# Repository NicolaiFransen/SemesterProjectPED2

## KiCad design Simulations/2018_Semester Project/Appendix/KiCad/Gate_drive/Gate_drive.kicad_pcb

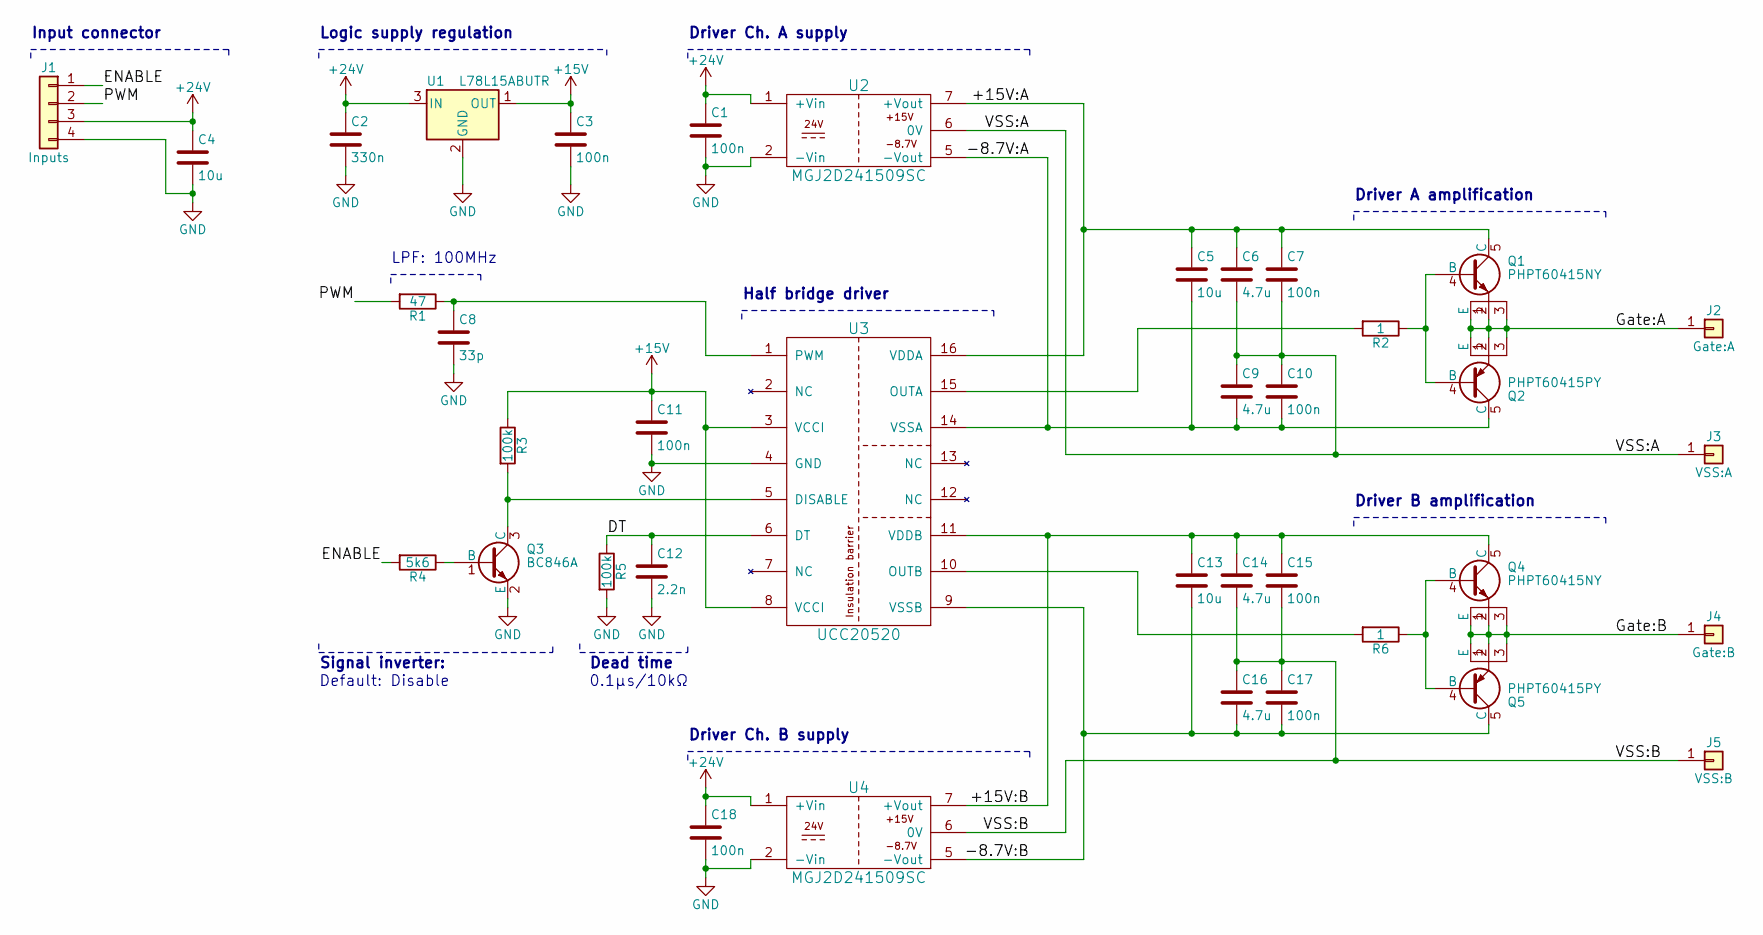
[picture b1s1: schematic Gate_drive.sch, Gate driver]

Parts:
C1, C3, C7, C10, C11, C15, C17, C18: 100n; C_1206
C2: 330n; C_1206
C4, C5, C13: 10u; C_1206
C6, C9, C14, C16: 4.7u; C_1206
C8: 33p; C_1206
C12: 2.2n; C_1206
J1: Inputs; Molex_KK-6410-04_04x2.54mm_Straight
J2: Gate:A; SolderWirePad_2x_1-2mmDrill
J3: VSS:A; SolderWirePad_single_1-2mmDrill
J4: Gate:B; SolderWirePad_2x_1-2mmDrill
J5: VSS:B; SolderWirePad_single_1-2mmDrill
Q1, Q4: PHPT60415NY; SOT-669_LFPAK
Q2, Q5: PHPT60415PY; SOT-669_LFPAK
Q3: BC846A; SOT-23
R1: 47; R_1206
R2, R6: 1; R_1206
R3, R5: 100k; R_1206
R4: 5k6; R_1206
U1: L78L15ABUTR; SOT-89-3
U2, U4: MGJ2D241509SC; SIL_MGJ2
U3: UCC20520; SOIC-16W_7.5x10.3mm_Pitch1.27mm

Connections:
+15V: C3.1, C11.1, R3.1, U1.1 (OUT), U3.3 (VCCI), U3.8 (VCCI)
+24V: C1.1, C2.1, C4.1, C18.1, J1.3, U1.3 (IN), U2.1 (+Vin), U4.1 (+Vin)
/+15V:A: C5.1, C6.1, C7.1, Q1.5 (C), U2.7 (+Vout), U3.16 (VDDA)
/+15V:B: C13.1, C14.1, C15.1, Q4.5 (C), U3.11 (VDDB), U4.7 (+Vout)
/-8.7V:A: C5.2, C9.2, C10.2, Q2.5 (C), U2.5 (-Vout), U3.14 (VSSA)
/-8.7V:B: C13.2, C16.2, C17.2, Q5.5 (C), U3.9 (VSSB), U4.5 (-Vout)
/DT: C12.1, R5.1, U3.6 (DT)
/ENABLE: J1.1, R4.2
/Gate:A: J2.1, Q1.1 (E), Q1.2, Q1.3, Q2.1 (E), Q2.2, Q2.3
/Gate:B: J4.1, Q4.1 (E), Q4.2, Q4.3, Q5.1 (E), Q5.2, Q5.3
/PWM: J1.2, R1.2
/VSS:A: C6.2, C7.2, C9.1, C10.1, J3.1, U2.6 (0V)
/VSS:B: C14.2, C15.2, C16.1, C17.1, J5.1, U4.6 (0V)
GND: C1.2, C2.2, C3.2, C4.2, C8.2, C11.2, C12.2, C18.2, J1.4, Q3.2 (E), R5.2, U1.2 (GND), U2.2 (-Vin), U3.4 (GND), U4.2 (-Vin)
unnamed: C8.1, R1.1, U3.1 (PWM)
unnamed: Q1.4 (B), Q2.4 (B), R2.1
unnamed: Q3.1 (B), R4.1
unnamed: Q3.3 (C), R3.2, U3.5 (DISABLE)
unnamed: Q4.4 (B), Q5.4 (B), R6.1
unnamed: R2.2, U3.15 (OUTA)
unnamed: R6.2, U3.10 (OUTB)

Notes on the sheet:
Dead time
LPF: 100MHz
Input connector
Logic supply regulation
Driver Ch. A supply
Driver Ch. B supply
Driver A amplification
Driver B amplification
Half bridge driver
Signal inverter:
0.1µs/10kΩ
Default: Disable

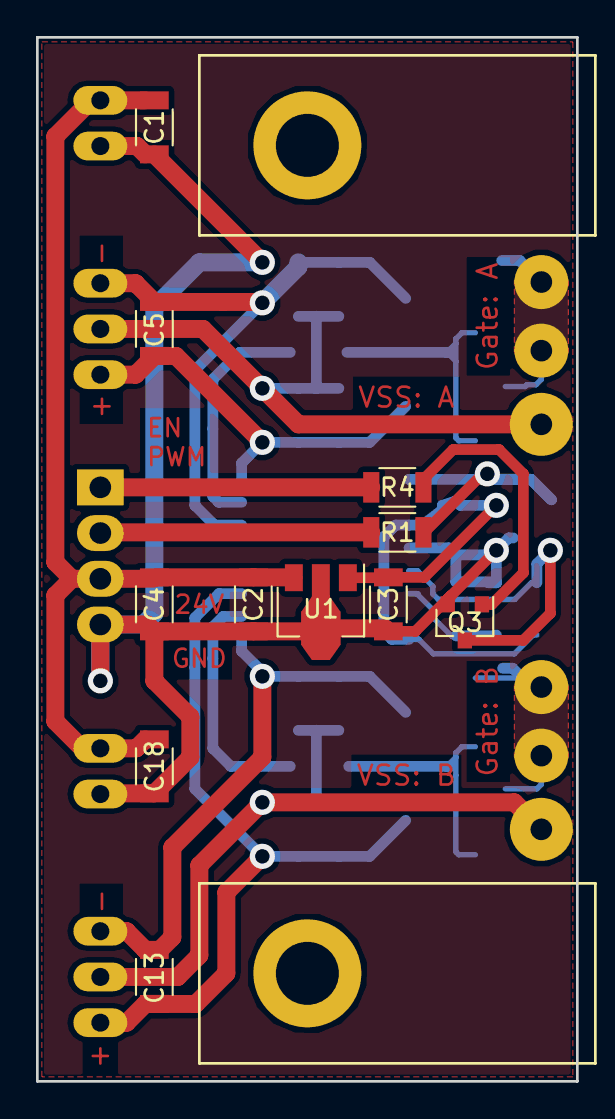
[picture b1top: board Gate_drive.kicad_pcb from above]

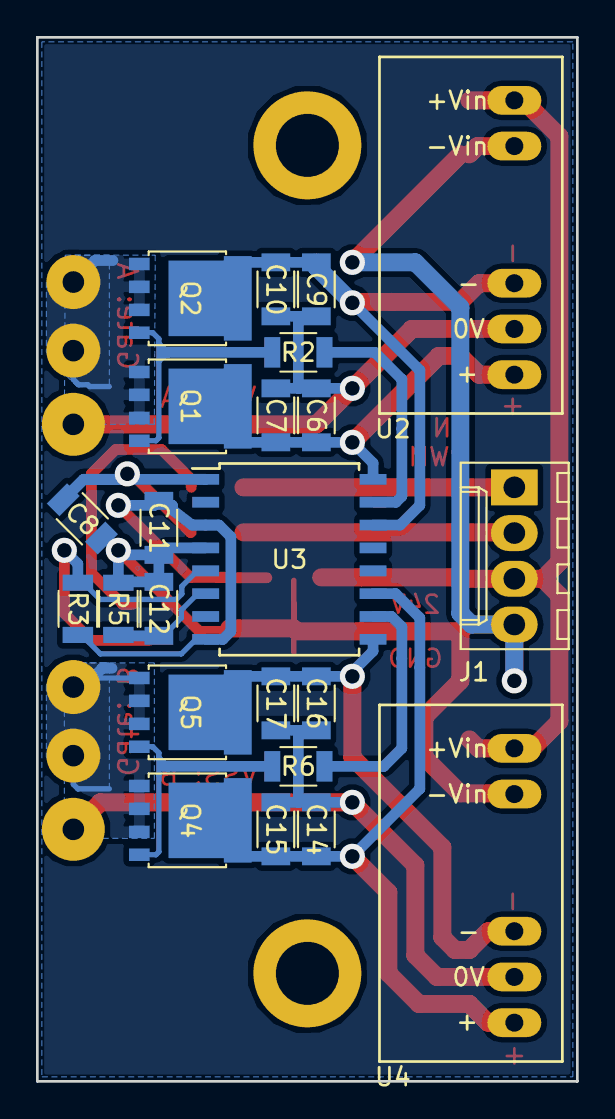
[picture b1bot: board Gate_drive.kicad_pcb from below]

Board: 2 copper layers, 30.0 x 58.0 mm, 38 parts (23 on the bottom side), 21 nets.

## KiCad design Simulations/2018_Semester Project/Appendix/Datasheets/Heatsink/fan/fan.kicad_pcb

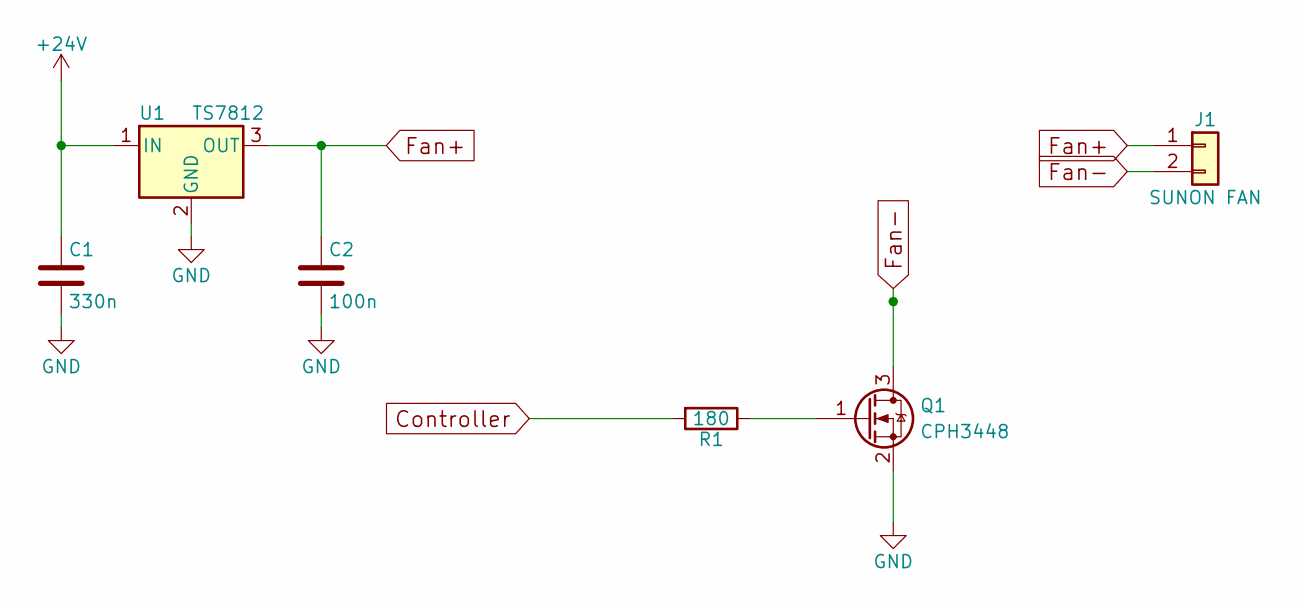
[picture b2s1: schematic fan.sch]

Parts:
C1: 330n; C_1206
C2: 100n; C_1206
J1: SUNON FAN; Molex_KK-6410-02_02x2.54mm_Straight
Q1: CPH3448; SOT-23
R1: 180; R_1206
U1: TS7812; TO-220-3_Horizontal

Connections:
+24V: C1.1, U1.1 (IN)
Controller: R1.2
Fan+: C2.1, J1.1, U1.3 (OUT)
Fan-: J1.2, Q1.3 (D)
GND: C1.2, C2.2, Q1.2 (S), U1.2 (GND)
unnamed: Q1.1 (G), R1.1

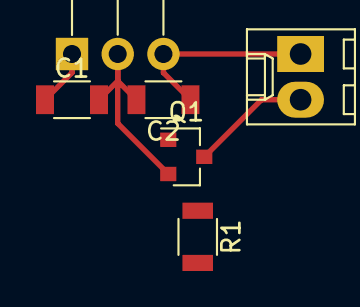
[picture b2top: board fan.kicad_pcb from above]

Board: 2 copper layers, 6 parts (0 on the bottom side), 5 nets.

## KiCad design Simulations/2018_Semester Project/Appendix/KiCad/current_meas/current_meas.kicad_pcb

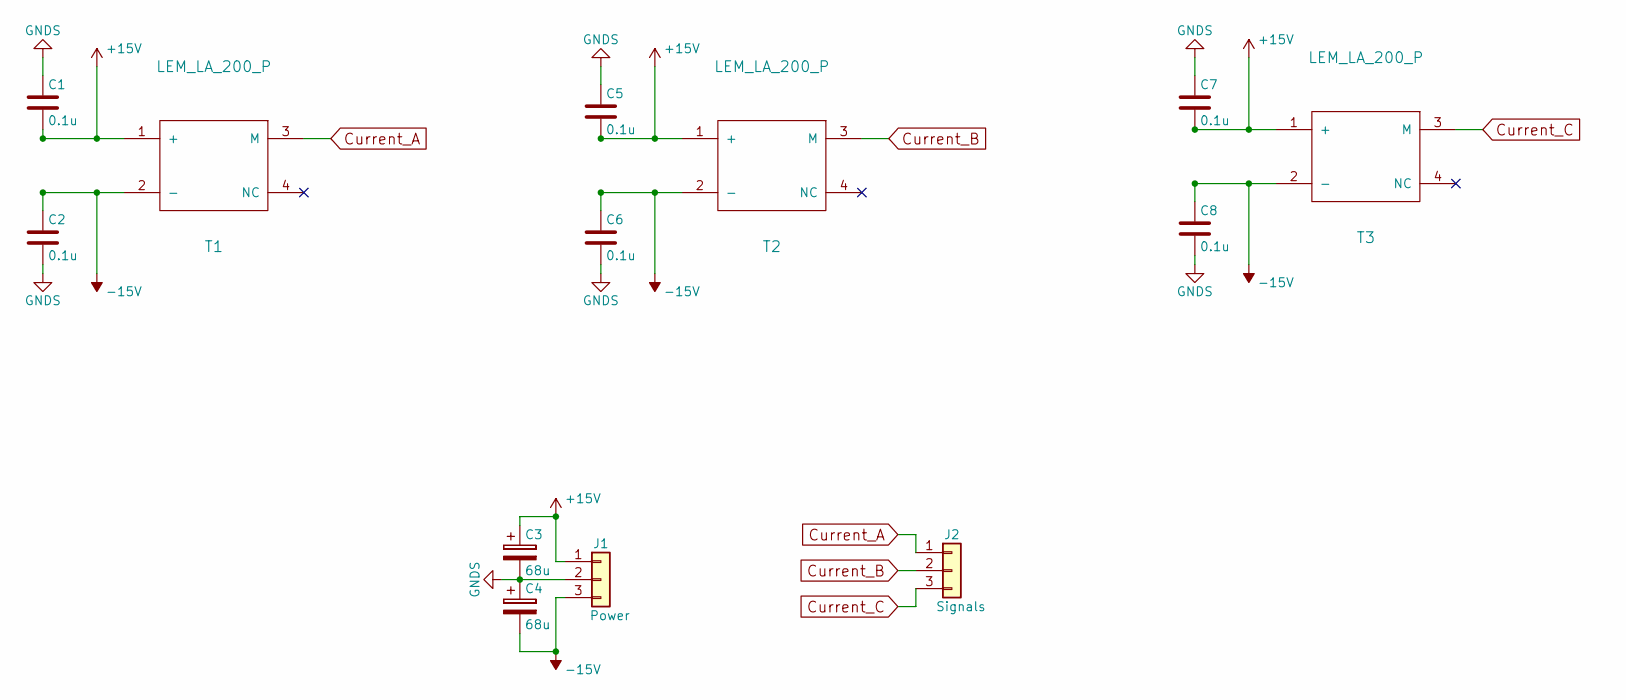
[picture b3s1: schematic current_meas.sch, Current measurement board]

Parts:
C1, C2, C5, C6, C7, C8: 0.1u; C_1206_HandSoldering
C3, C4: 68u; CP_Radial_D6.3mm_P2.50mm
J1: Power; Molex_KK-6410-03_03x2.54mm_Straight
J2: Signals; Molex_KK-6410-03_03x2.54mm_Straight
T1, T2, T3: LEM_LA_200_P; LEM_200

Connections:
+15V: C1.2, C3.1, C5.2, C7.2, J1.1, T1.1 (+), T2.1 (+), T3.1 (+)
-15V: C2.1, C4.2, C6.1, C8.1, J1.3, T1.2 (-), T2.2 (-), T3.2 (-)
Current_A: J2.1, T1.3 (M)
Current_B: J2.2, T2.3 (M)
Current_C: J2.3, T3.3 (M)
GNDS: C1.1, C2.2, C3.2, C4.1, C5.1, C6.2, C7.1, C8.2, J1.2

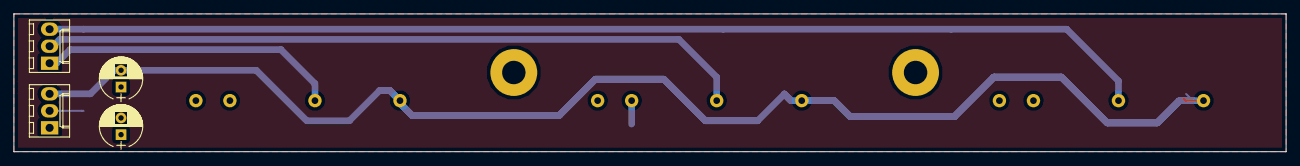
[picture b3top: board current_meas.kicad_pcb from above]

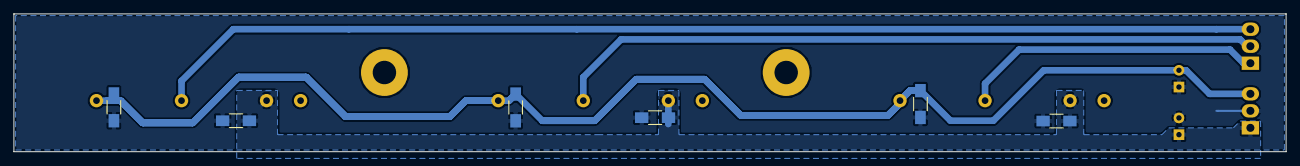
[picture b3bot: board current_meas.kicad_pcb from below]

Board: 2 copper layers, 190.0 x 20.6 mm, 13 parts (6 on the bottom side), 6 nets.

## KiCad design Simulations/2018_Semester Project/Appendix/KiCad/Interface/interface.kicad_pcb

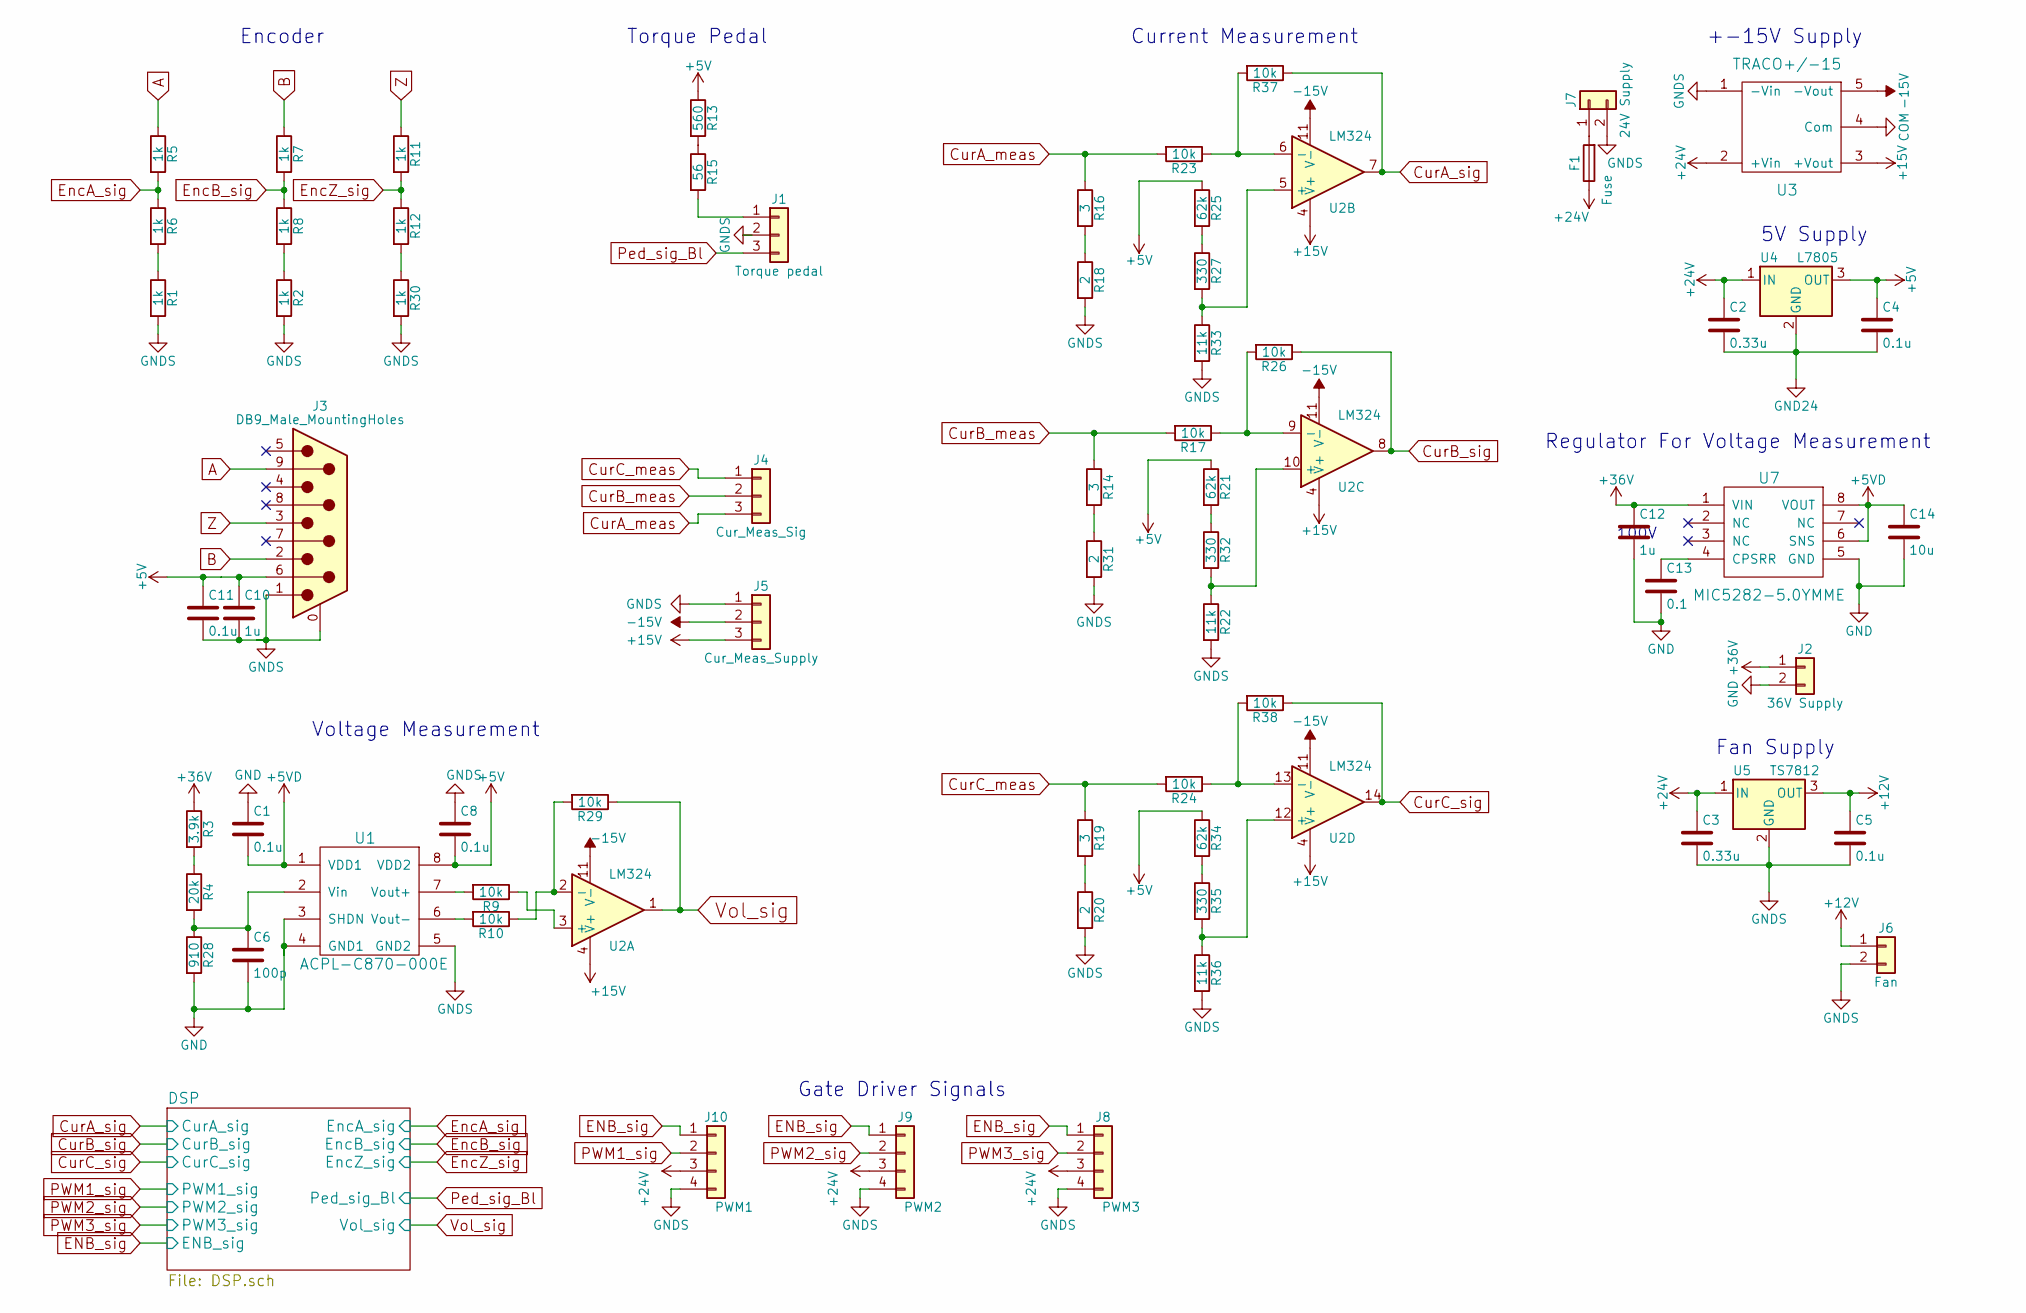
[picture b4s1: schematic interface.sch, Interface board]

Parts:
C1, C4, C5, C8, C11: 0.1u; C_1206
C2, C3: 0.33u; C_1206
C6: 100p; C_1206
C10, C12: 1u; C_1206
C13: 0.1; C_1206
C14: 10u; C_1206
F1: Fuse; Fuseholder5x20_horiz_open_Schurter_0031_8201
J1: Torque pedal; Molex_KK-6410-03_03x2.54mm_Straight
J2: 36V Supply; Molex_KK-6410-02_02x2.54mm_Straight
J3: DB9_Male_MountingHoles; DMR-09-P
J4: Cur_Meas_Sig; Molex_KK-6410-03_03x2.54mm_Straight
J5: Cur_Meas_Supply; Molex_KK-6410-03_03x2.54mm_Straight
J6: Fan; Molex_KK-6410-02_02x2.54mm_Straight
J7: 24V Supply; Molex_KK-6410-02_02x2.54mm_Straight
J8: PWM3; Molex_KK-6410-04_04x2.54mm_Straight
J9: PWM2; Molex_KK-6410-04_04x2.54mm_Straight
J10: PWM1; Molex_KK-6410-04_04x2.54mm_Straight
R1, R2, R5, R6, R7, R8, R11, R12, R30: 1k; R_1206
R3: 3.9k; R_1206
R4: 20k; R_1206
R9, R10, R17, R23, R24, R26, R29, R37, R38: 10k; R_1206
R13: 560; R_1206
R14, R16, R19: 3; R_1206
R15: 56; R_1206
R18, R20, R31: 2; R_1206
R21, R25, R34: 62k; R_1206
R22, R33, R36: 11k; R_1206
R27, R32, R35: 330; R_1206
R28: 910; R_1206
U1: ACPL-C870-000E
U2: LM324; SOIC-14_3.9x8.7mm_Pitch1.27mm
U3: TRACO+/-15; DCDC-Conv_TRACO_TEN10-XXXX_Dual
U4: L7805; TO-220-3_Horizontal
U5: TS7812; TO-220-3_Horizontal
U7: MIC5282-5.0YMME; 8-Pin(ePad)MSOP

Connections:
+5V: C4.1, C8.2, C10.1, C11.1, J3.6, R13.1, R21.1, R25.1, R34.1, U1.8 (VDD2), U4.3 (OUT); also elsewhere on the board
+5VD: C1.2, C14.1, U1.1 (VDD1), U7.6 (SNS), U7.8 (VOUT)
+12V: C5.1, J6.1, U5.3 (OUT)
+15V: J5.3, U2.4 (V+), U3.3 (+Vout)
+24V: C2.1, C3.1, F1.1, J8.3, J9.3, J10.3, U3.2 (+Vin), U4.1 (IN), U5.1 (IN)
+36V: C12.1, J2.1, R3.1, U7.1 (VIN)
-15V: J5.2, U2.11 (V-), U3.5 (-Vout)
A: J3.9, R5.1
B: J3.2, R7.1
CurA_meas: J4.3, R16.1, R23.2
CurA_sig: R37.1, U2.7; also elsewhere on the board
CurB_meas: J4.2, R14.1, R17.2
CurB_sig: R26.1, U2.8; also elsewhere on the board
CurC_meas: J4.1, R19.1, R24.2
CurC_sig: R38.1, U2.14; also elsewhere on the board
ENB_sig: J8.1, J9.1, J10.1; also elsewhere on the board
EncA_sig: R5.2, R6.1; also elsewhere on the board
EncB_sig: R7.2, R8.1; also elsewhere on the board
EncZ_sig: R11.2, R12.1; also elsewhere on the board
GND: C1.1, C6.2, C12.2, C13.2, C14.2, J2.2, R28.2, U1.3 (SHDN), U1.4 (GND1), U7.5 (GND)
unnamed: C6.1, R4.2, R28.1, U1.2 (Vin)
unnamed: C13.1, U7.4 (CPSRR)
unnamed: F1.2, J7.1
unnamed: J1.1, R15.2
unnamed: R1.1, R6.2
unnamed: R2.1, R8.2
unnamed: R3.2, R4.1
unnamed: R9.1, U2.3 (+)
unnamed: R9.2, U1.7 (Vout+)
unnamed: R10.1, R29.2, U2.2 (-)
unnamed: R10.2, U1.6 (Vout-)
unnamed: R12.2, R30.1
unnamed: R13.2, R15.1
unnamed: R14.2, R31.1
unnamed: R16.2, R18.1
unnamed: R17.1, R26.2, U2.9 (-)
unnamed: R19.2, R20.1
unnamed: R21.2, R32.1
unnamed: R22.1, R32.2, U2.10 (+)
unnamed: R23.1, R37.2, U2.6 (-)
unnamed: R24.1, R38.2, U2.13 (-)
unnamed: R25.2, R27.1
unnamed: R27.2, R33.1, U2.5 (+)
unnamed: R34.2, R35.1
unnamed: R35.2, R36.1, U2.12 (+)
PWM1_sig: J10.2; also elsewhere on the board
PWM2_sig: J9.2; also elsewhere on the board
PWM3_sig: J8.2; also elsewhere on the board
Ped_sig_Bl: J1.3; also elsewhere on the board
Vol_sig: R29.1, U2.1; also elsewhere on the board
Z: J3.3, R11.1

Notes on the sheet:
Torque Pedal
Encoder
Voltage Measurement
Fan Supply
100V
Regulator For Voltage Measurement
Gate Driver Signals
5V Supply
Current Measurement
+-15V Supply

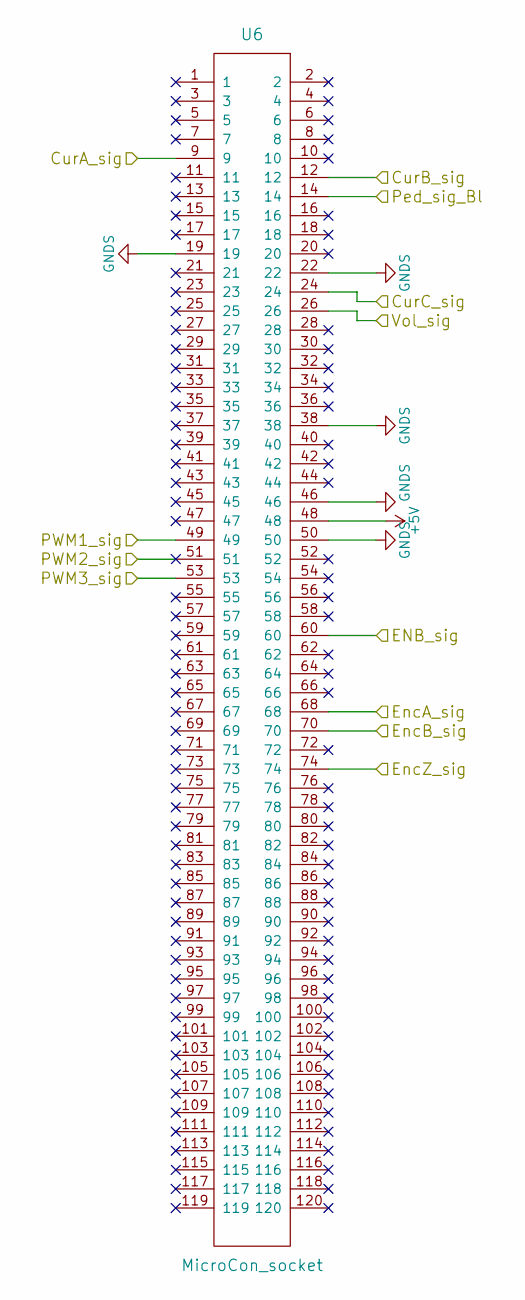
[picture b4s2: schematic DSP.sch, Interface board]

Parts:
U6: MicroCon_socket; HSEC8-160-01-L-DV-A

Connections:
+5V: U6.48; also elsewhere on the board
CurA_sig: U6.9; also elsewhere on the board
CurB_sig: U6.12; also elsewhere on the board
CurC_sig: U6.24; also elsewhere on the board
ENB_sig: U6.60; also elsewhere on the board
EncA_sig: U6.68; also elsewhere on the board
EncB_sig: U6.70; also elsewhere on the board
EncZ_sig: U6.74; also elsewhere on the board
PWM1_sig: U6.49; also elsewhere on the board
PWM2_sig: U6.51; also elsewhere on the board
PWM3_sig: U6.53; also elsewhere on the board
Ped_sig_Bl: U6.14; also elsewhere on the board
Vol_sig: U6.26; also elsewhere on the board

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
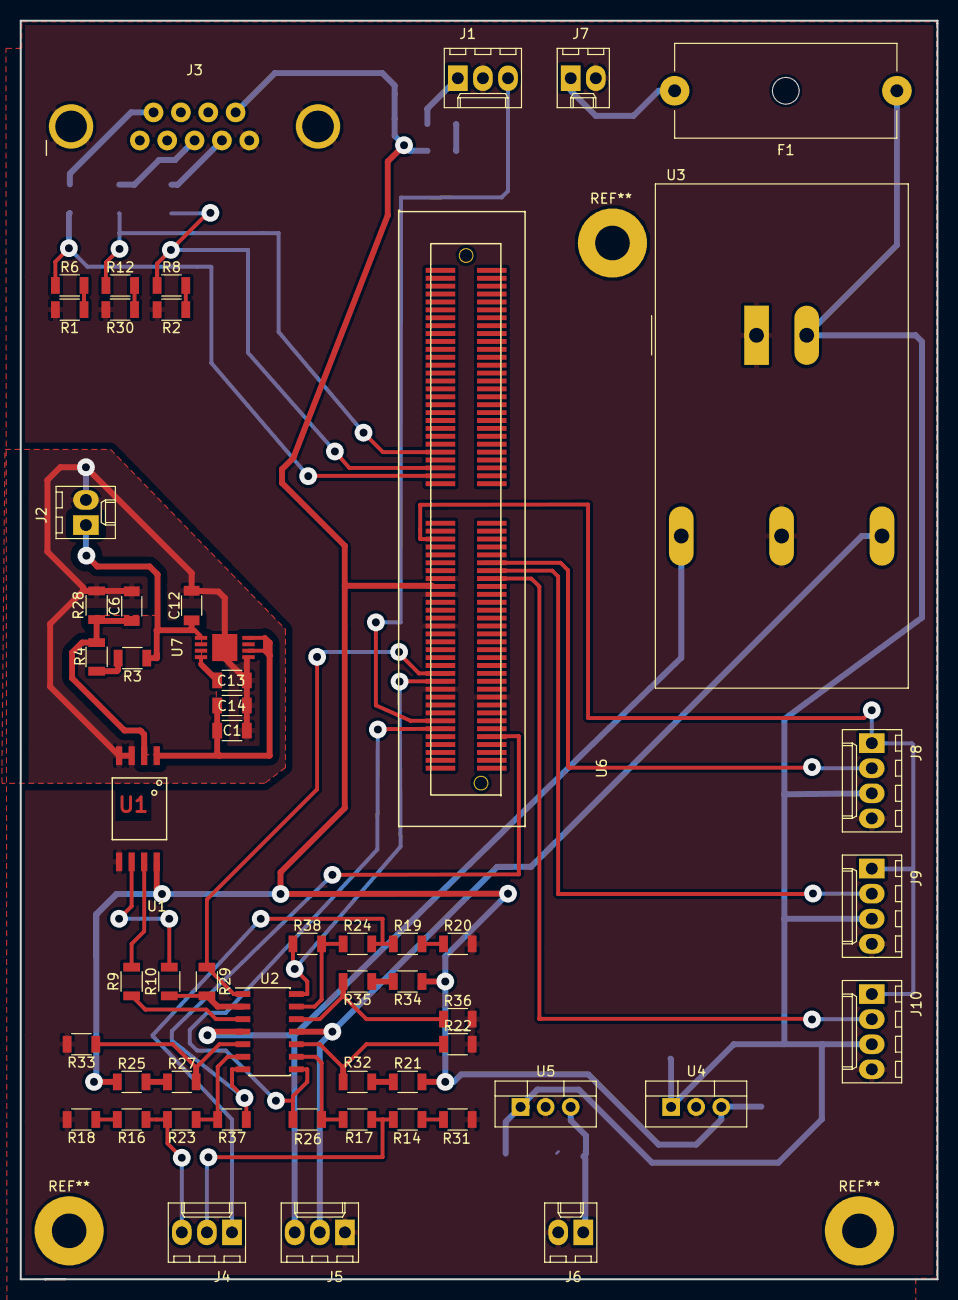
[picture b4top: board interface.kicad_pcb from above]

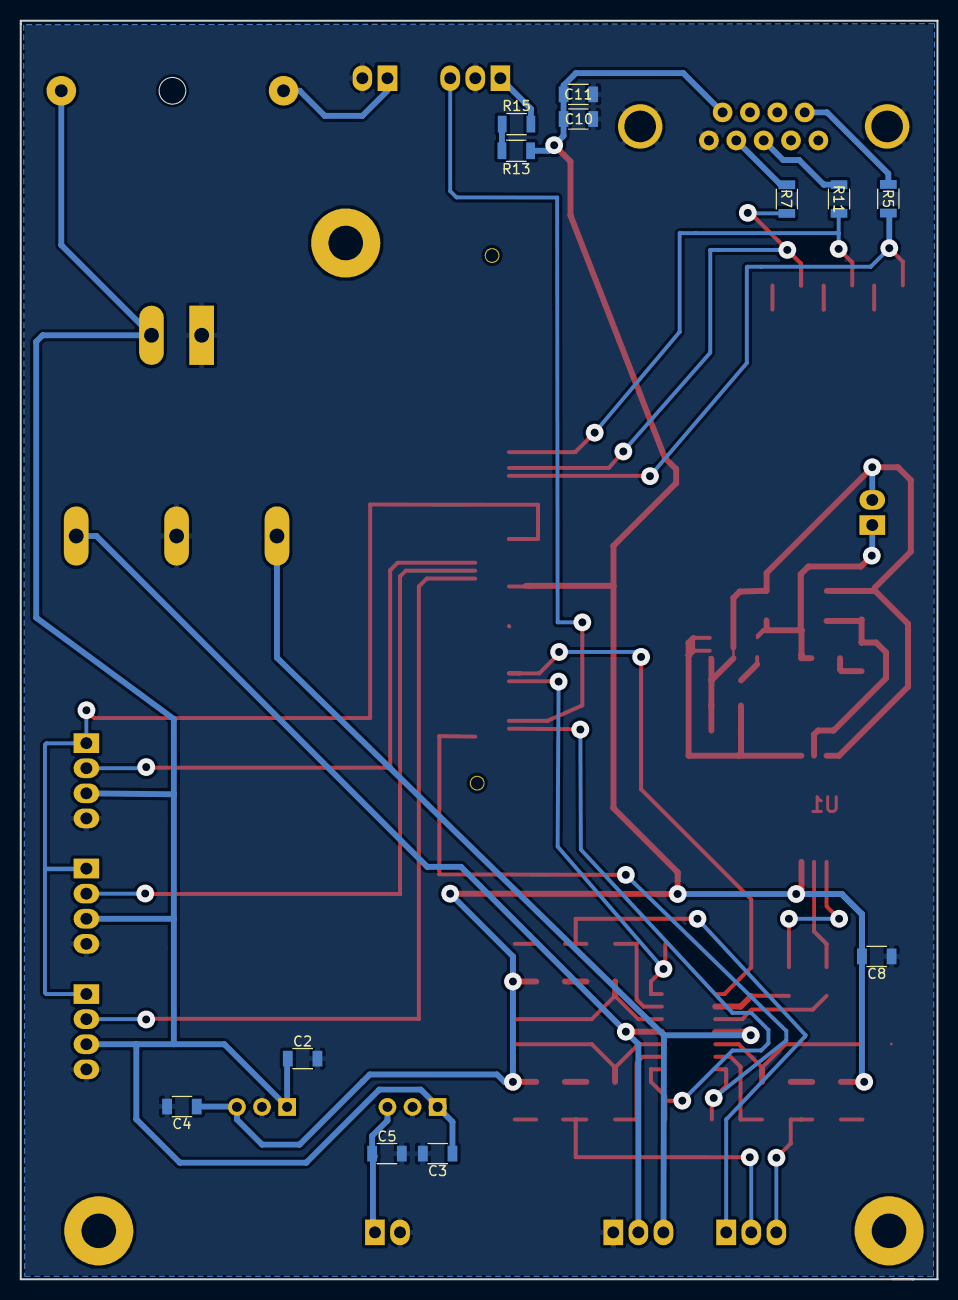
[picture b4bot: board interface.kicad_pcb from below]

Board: 2 copper layers, 92.8 x 127.4 mm, 68 parts (12 on the bottom side), 52 nets.

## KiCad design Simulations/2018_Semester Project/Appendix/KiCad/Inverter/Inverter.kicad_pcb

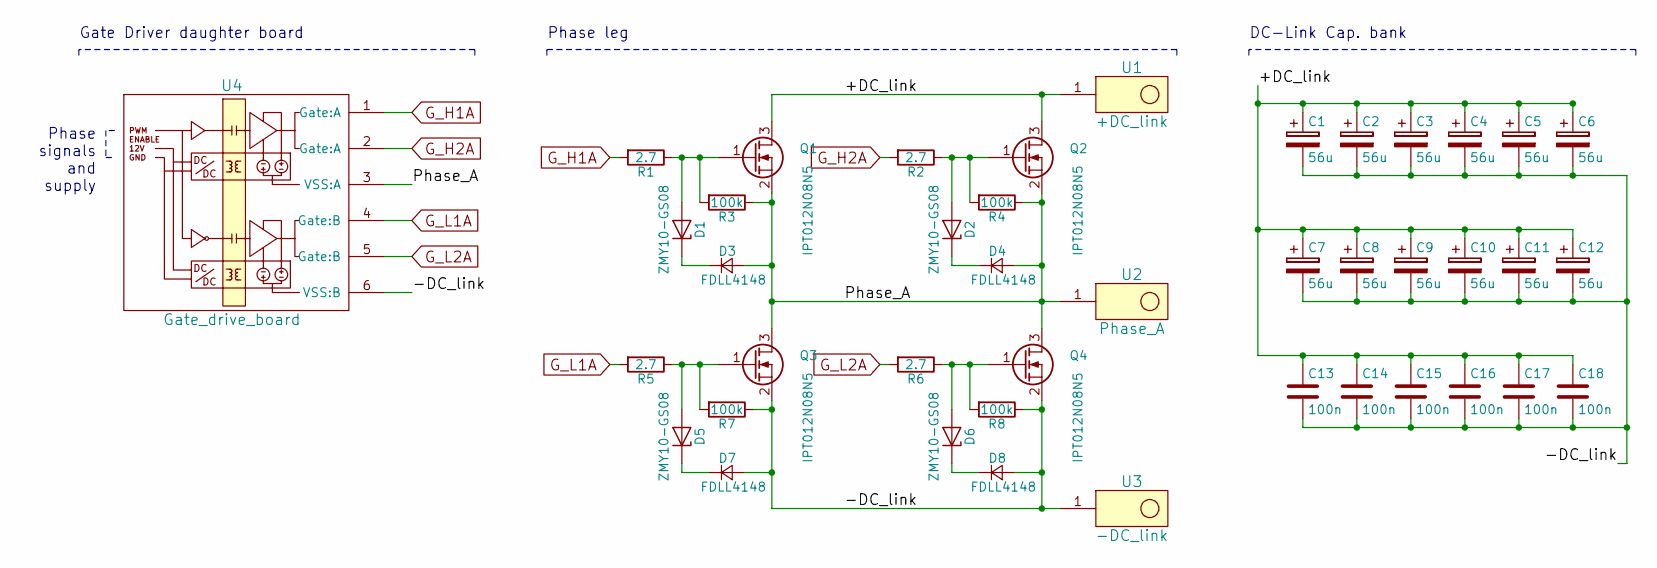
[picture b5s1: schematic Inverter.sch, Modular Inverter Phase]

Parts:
C1, C2, C3, C4, C5, C6, C7, C8, C9, C10, C11, C12: 56u; CP_Elec_10x10.5
C13, C14, C15, C16, C17, C18: 100n; C_1206
D1, D2, D5, D6: ZMY10-GS08; D_MELF
D3, D4, D7, D8: FDLL4148; D_MiniMELF
Q1, Q2, Q3, Q4: IPT012N08N5; Infineon_PG-HSOF-8-1
R1, R2, R5, R6: 2.7; R_1206
R3, R4, R7, R8: 100k; R_1206
U1: +DC_link; cu_bar_long
U2: Phase_A; cu_bar
U3: -DC_link; cu_bar_long
U4: Gate_drive_board; Gate_driver_example

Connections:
/+DC_link: C1.1, C2.1, C3.1, C4.1, C5.1, C6.1, C7.1, C8.1, C9.1, C10.1, C11.1, C12.1, C13.1, C14.1, C15.1, C16.1, C17.1, C18.1, Q1.3 (D), Q2.3 (D), U1.1
/-DC_link: C1.2, C2.2, C3.2, C4.2, C5.2, C6.2, C7.2, C8.2, C9.2, C10.2, C11.2, C12.2, C13.2, C14.2, C15.2, C16.2, C17.2, C18.2, D7.2 (A), D8.2 (A), Q3.2 (S), Q4.2 (S), R7.1, R8.1, U3.1, U4.6 (VSS:B)
/Phase_A: D3.2 (A), D4.2 (A), Q1.2 (S), Q2.2 (S), Q3.3 (D), Q4.3 (D), R3.1, R4.1, U2.1, U4.3 (VSS:A)
G_H1A: R1.2, U4.1 (Gate:A)
G_H2A: R2.2, U4.2 (Gate:A)
G_L1A: R5.2, U4.4 (Gate:B)
G_L2A: R6.2, U4.5 (Gate:B)
unnamed: D1.1 (K), D3.1 (K)
unnamed: D1.2 (A), Q1.1 (G), R1.1, R3.2
unnamed: D2.1 (K), D4.1 (K)
unnamed: D2.2 (A), Q2.1 (G), R2.1, R4.2
unnamed: D5.1 (K), D7.1 (K)
unnamed: D5.2 (A), Q3.1 (G), R5.1, R7.2
unnamed: D6.1 (K), D8.1 (K)
unnamed: D6.2 (A), Q4.1 (G), R6.1, R8.2

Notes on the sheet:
Phase leg
Phase signals and supply
DC-Link Cap. bank
Gate Driver daughter board

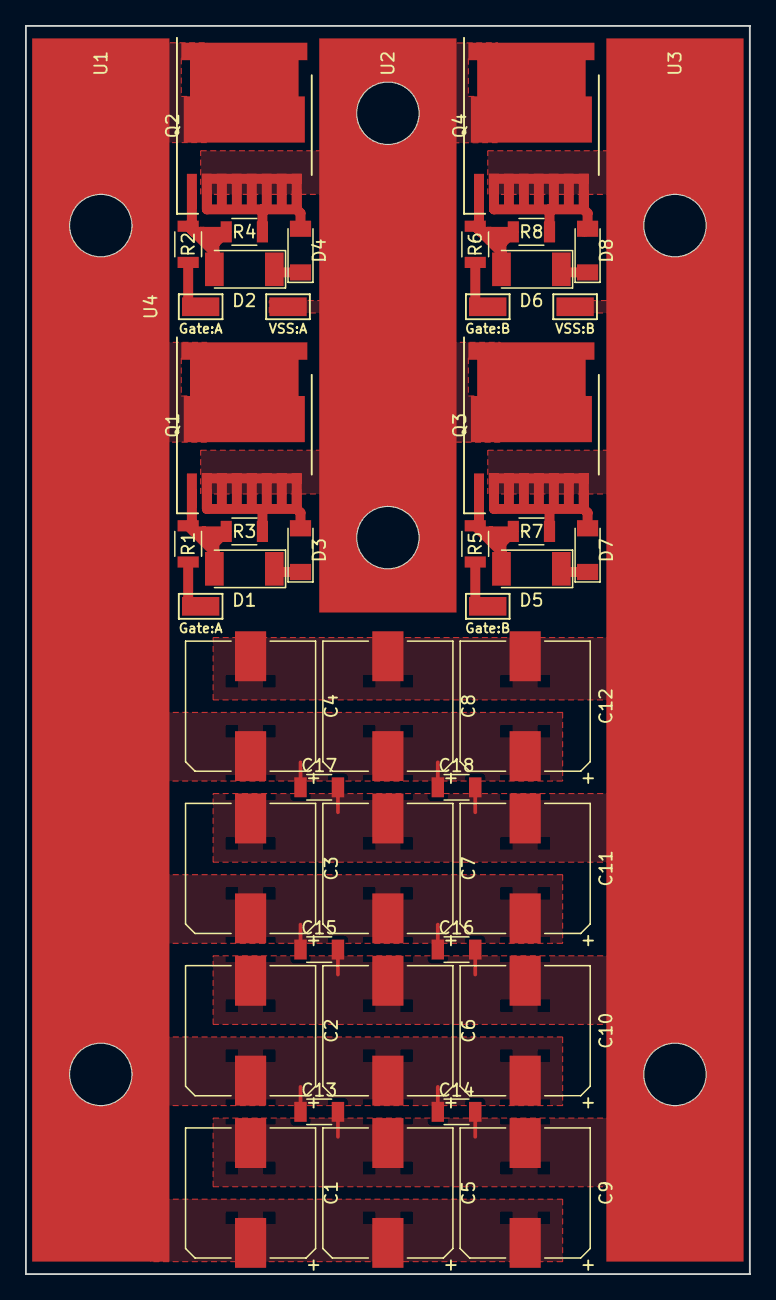
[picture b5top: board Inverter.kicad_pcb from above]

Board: 2 copper layers, 58.0 x 100.0 mm, 42 parts (0 on the bottom side), 15 nets.

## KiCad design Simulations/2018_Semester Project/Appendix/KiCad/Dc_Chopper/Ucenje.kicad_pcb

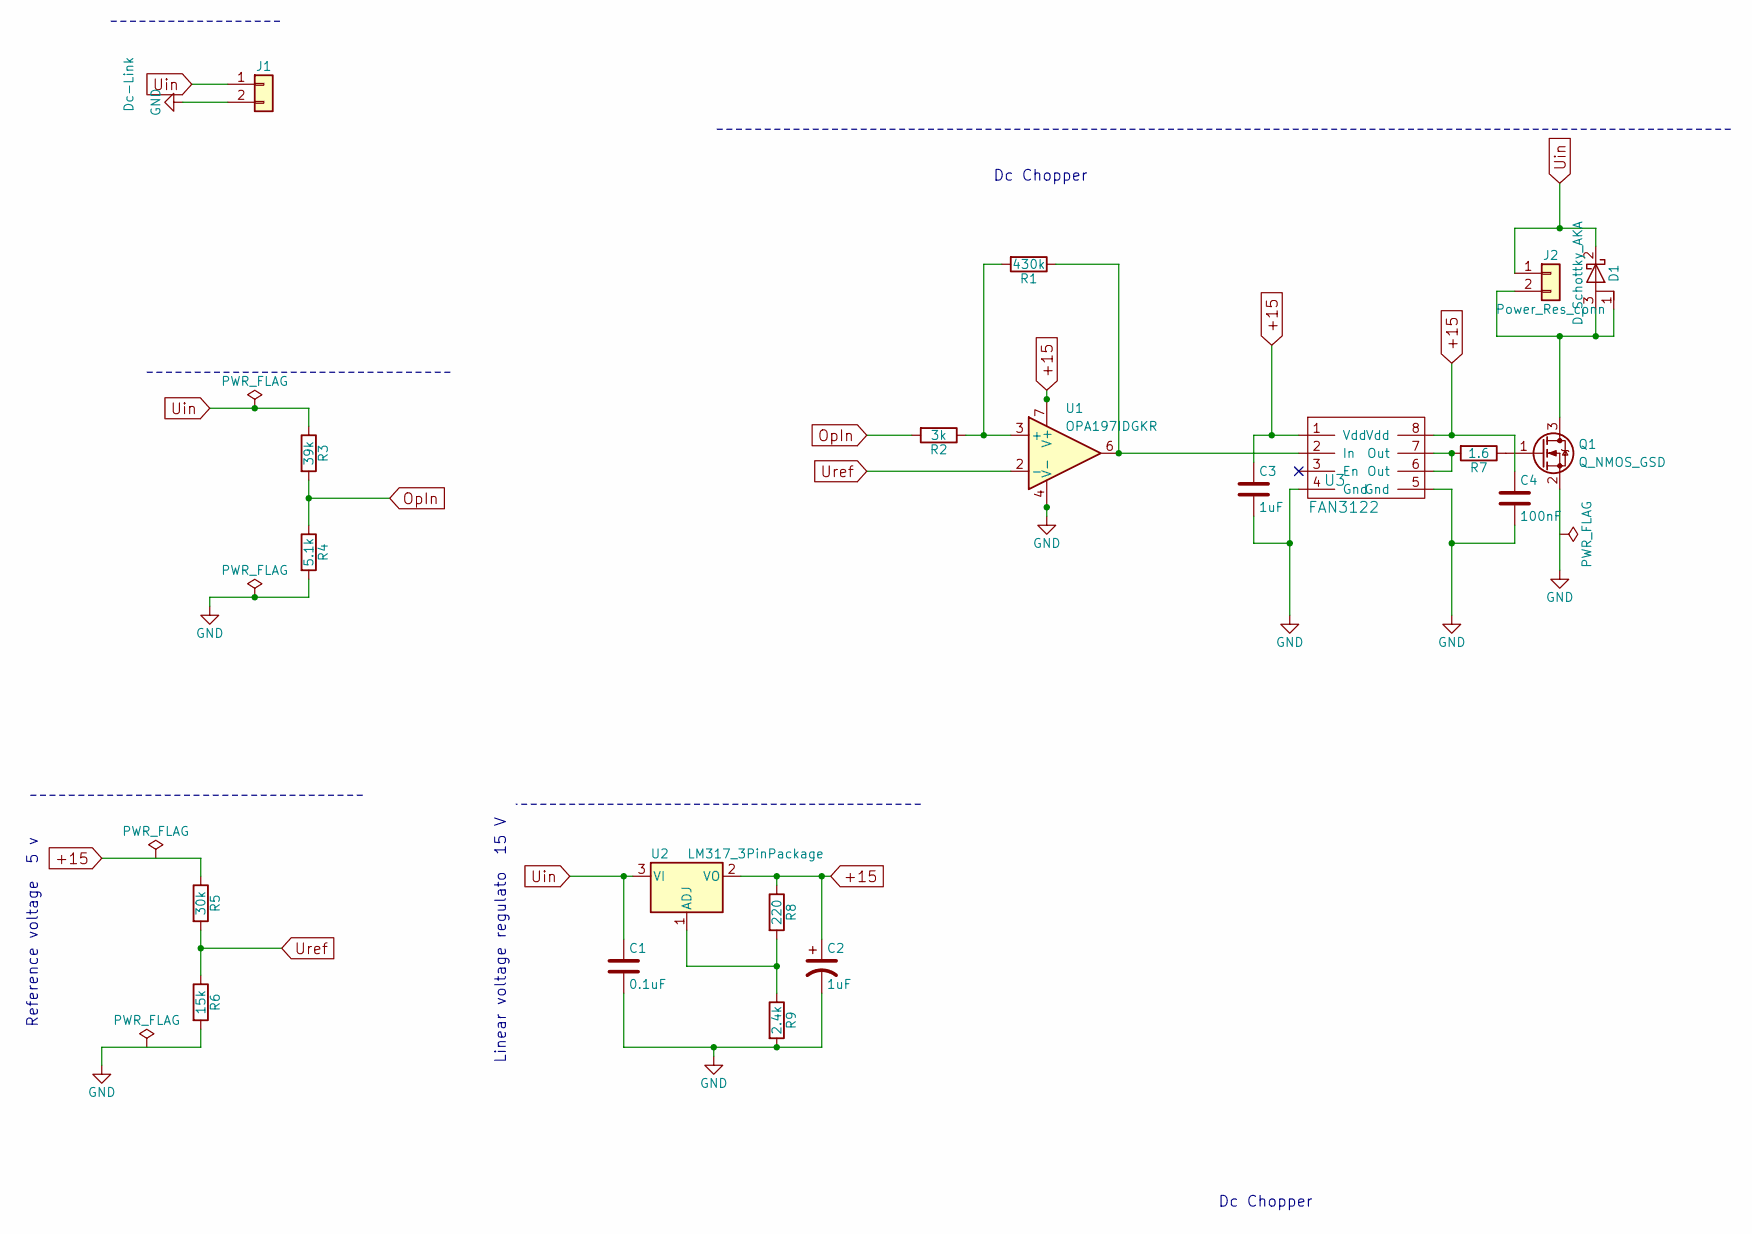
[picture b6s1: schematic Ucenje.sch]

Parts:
C1: 0.1uF; C_1210
C2: 1uF; C_1210
C3: 1uF; C_1206
C4: 100nF; C_1206
D1: D_Schottky_AKA; TO-220-3_Vertical
J1: Dc-Link; WireConnection_2.50mmDrill
J2: Power_Res_conn; WireConnection_2.50mmDrill
Q1: Q_NMOS_GSD; Infineon_PG-HSOF-8-1
R1: 430k; R_1206
R2: 3k; R_1206
R3: 39k; R_1206
R4: 5.1k; R_1206
R5: 30k; R_1206
R6: 15k; R_1206
R7: 1.6; R_1206
R8: 220; R_1206
R9: 2.4k; R_1206
U1: OPA197IDGKR; VSSOP-8_3.0x3.0mm_Pitch0.65mm
U2: LM317_3PinPackage; TO-220-3_Vertical
U3: FAN3122; SOIC-8_3.9x4.9mm_Pitch1.27mm

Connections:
+15: C2.1, C3.1, C4.1, R5.1, R8.1, U1.7 (V+), U2.2 (VO), U3.1 (Vdd), U3.8 (Vdd)
GND: C1.2, C2.2, C3.2, C4.2, J1.2, Q1.2 (S), R4.2, R6.2, R9.2, U1.4 (V-), U3.4 (Gnd), U3.5 (Gnd)
unnamed: D1.1 (A), D1.3 (A), J2.2, Q1.3 (D)
unnamed: Q1.1 (G), R7.1
unnamed: R1.1, U1.6, U3.2 (In)
unnamed: R1.2, R2.1, U1.3 (+)
unnamed: R7.2, U3.6 (Out), U3.7 (Out)
unnamed: R8.2, R9.1, U2.1 (ADJ)
OpIn: R2.2, R3.2, R4.1
Uin: C1.1, D1.2 (K), J1.1, J2.1, R3.1, U2.3 (VI)
Uref: R5.2, R6.1, U1.2 (-)

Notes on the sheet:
Dc Chopper
Linear voltage regulato 15 V
Reference voltage 5 v
Dc Chopper

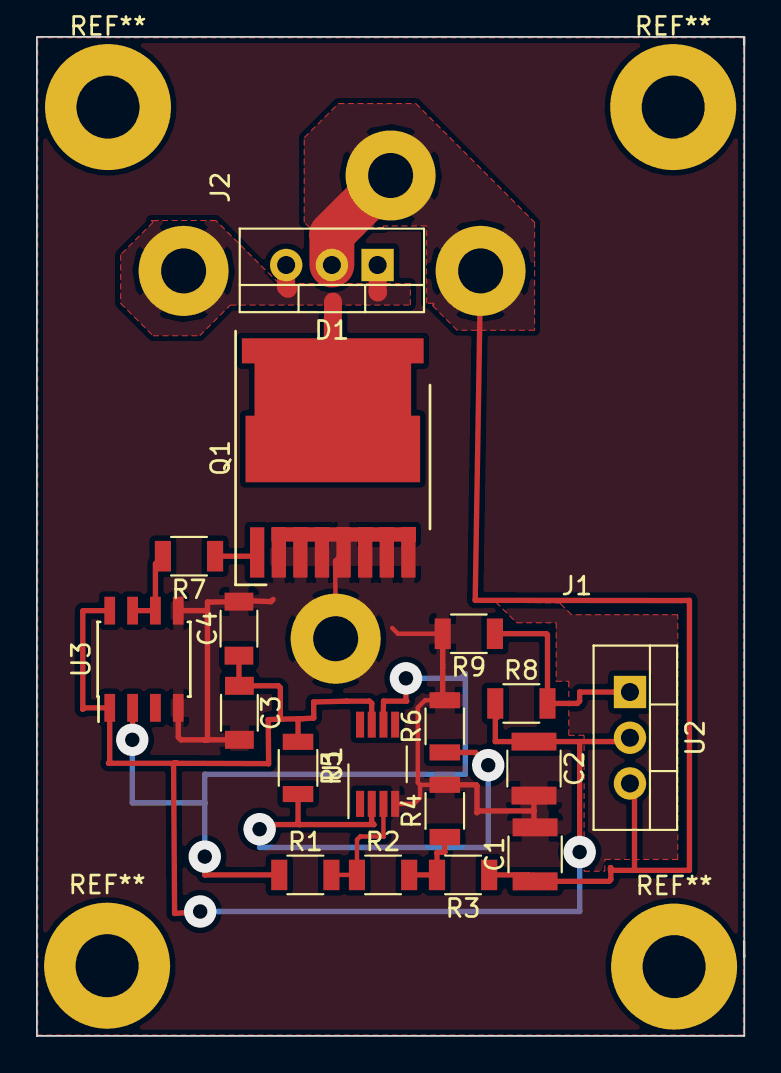
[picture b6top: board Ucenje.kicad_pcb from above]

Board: 2 copper layers, 39.3 x 55.5 mm, 20 parts (0 on the bottom side), 11 nets.
